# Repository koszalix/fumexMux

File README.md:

# Fumex Mux
Soldering station stand detection mux, for the [Fumex Project](https://github.com/koszalix/fumex)

# Licensing

This project is published under the Apache-2.0 license.

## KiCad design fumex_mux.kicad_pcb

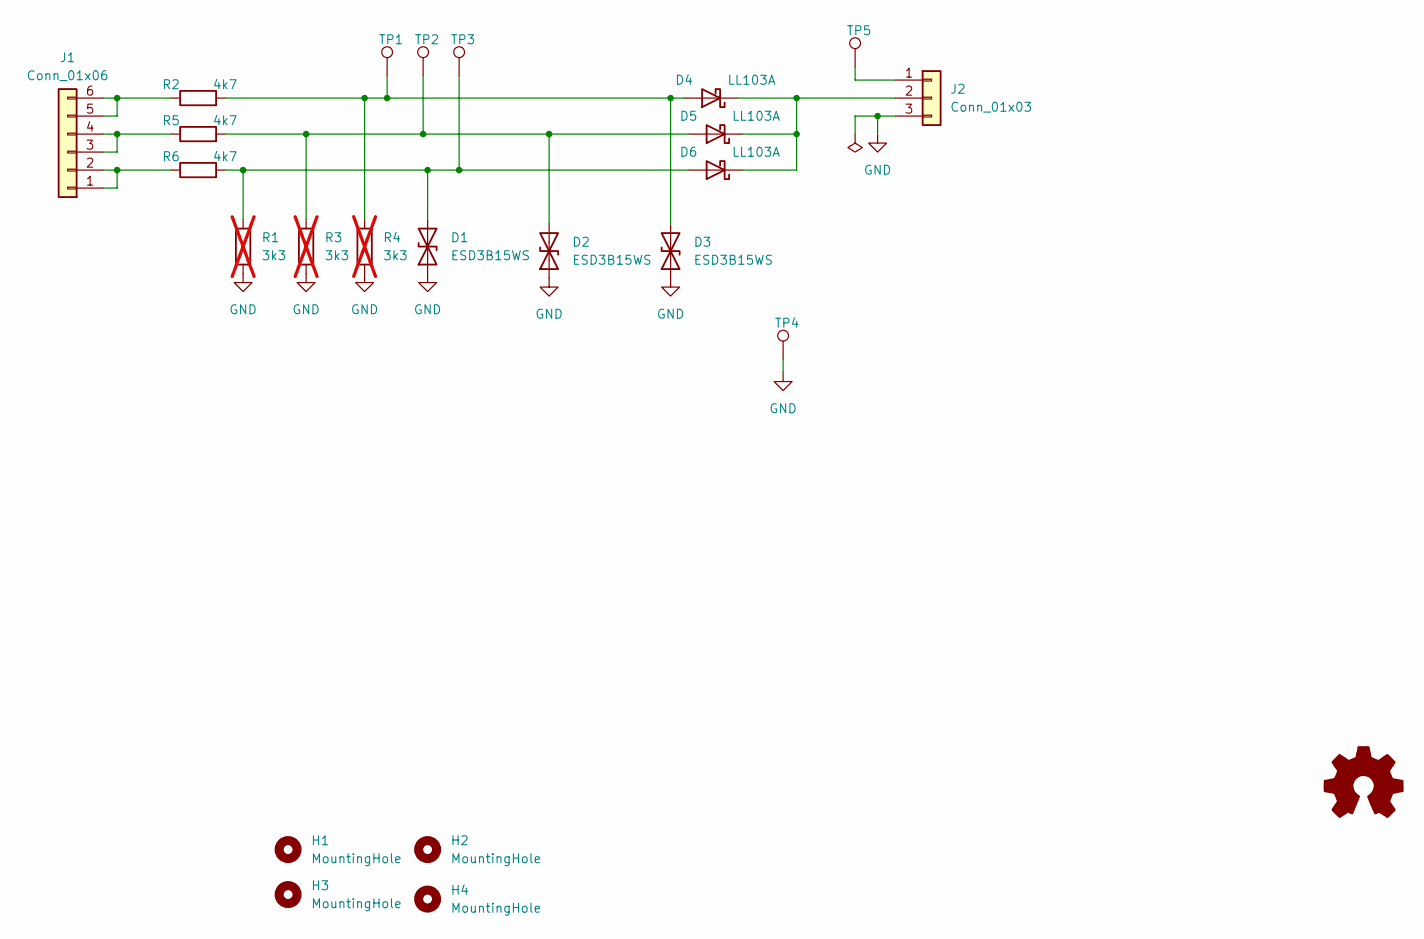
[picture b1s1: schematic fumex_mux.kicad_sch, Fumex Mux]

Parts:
D1, D2, D3: ESD3B15WS; D_SOD-323_HandSoldering
D4, D5, D6: LL103A; D_MiniMELF; MPN LL103A
H1, H2, H3, H4: MountingHole; MountingHole_3.2mm_M3
J1: Conn_01x06; SolderWire-0.25sqmm_1x06_P4.2mm_D0.65mm_OD1.7mm_Relief
J2: Conn_01x03; PinSocket_1x03_P2.54mm_Vertical
R1, R3, R4: 3k3; R_0603_1608Metric; Tolerance 1%; MPN RC0603FR-073k3; not fitted
R2, R5, R6: 4k7; R_0603_1608Metric; Tolerance 1%; MPN RC0603FR-074k7
TP1, TP2, TP3, TP4, TP5: TestPoint; TestPoint_Pad_D1.0mm

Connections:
GND: D1.1 (A1), D2.1 (A1), D3.1 (A1), J2.3, R1.1, R3.1, R4.1, TP4.1
unnamed: D1.2 (A2), D6.2 (A), R1.2, R6.2, TP3.1
unnamed: D2.2 (A2), D5.2 (A), R3.2, R5.2, TP2.1
unnamed: D3.2 (A2), D4.2 (A), R2.2, R4.2, TP1.1
unnamed: D4.1 (K), D5.1 (K), D6.1 (K), J2.2
unnamed: J1.1, J1.2, R6.1
unnamed: J1.3, J1.4, R5.1
unnamed: J1.5, J1.6, R2.1
unnamed: J2.1, TP5.1

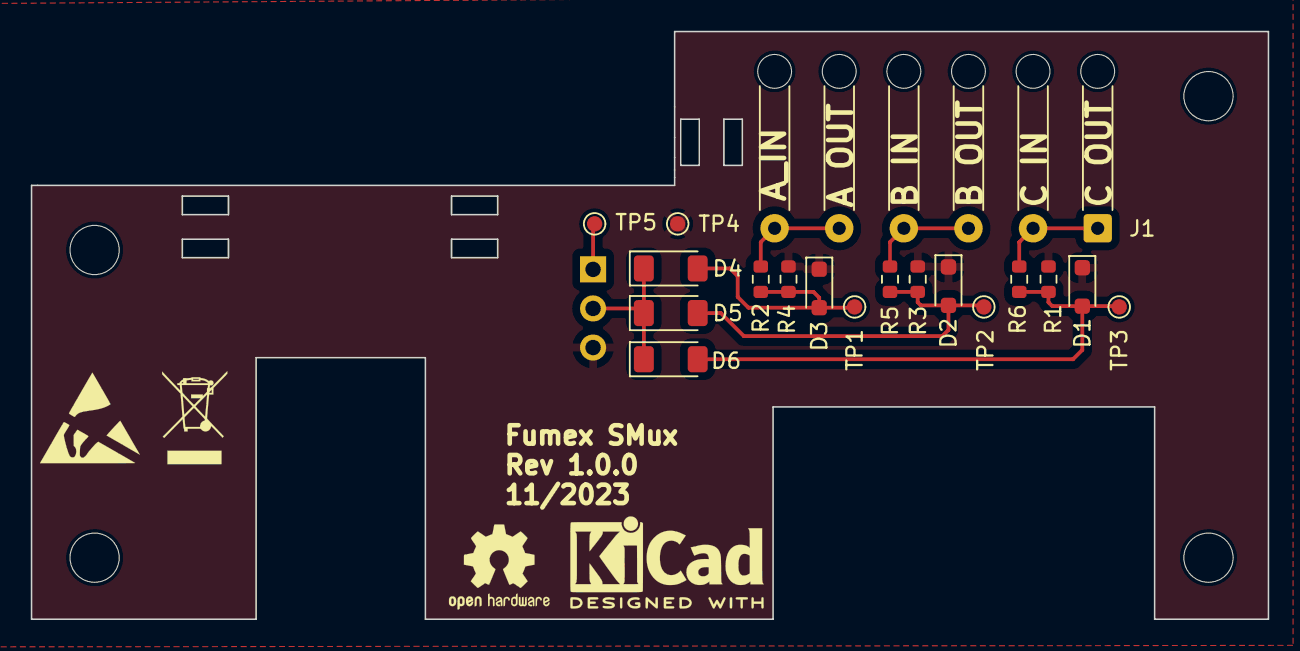
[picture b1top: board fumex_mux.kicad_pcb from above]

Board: 2 copper layers, 80.4 x 38.2 mm, 23 parts (1 on the bottom side), 9 nets.

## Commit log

2023-11-21 Revision 1.0.0 release
2023-11-21 Rename fumex png
2023-11-22 Add Licensing to REAME.md
2023-11-22 Add Changelog
